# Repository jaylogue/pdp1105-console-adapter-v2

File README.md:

# PDP-11/05 Console Adapter

The *PDP-11/05 Console Adapter* is a hardware device which acts as a USB and RS-232 serial interface to the console of a [PDP-11/05](http://gunkies.org/wiki/PDP-11/05) minicomputer. The Console Adapter provides a number of useful features for working with the PDP-11/05:

- **Direct connection to the SCL connector on the back of the PDP-11/05**
- **USB-to-serial functionality, allowing access to the PDP-11 console from a modern terminal program**
- **Auxiliary RS-232 interface for connecting a real serial terminal**
- **External baud clock generator, allowing console data rates greater than 2400 bps**
- **Dynamically adjustable serial data rate and format (110 to 38400 bps, 8-N-2, 7-E-2, 7-O-2)**
- **Virtual paper tape reader compatible with the 11/05's READER RUN signal**
- **M9312/M9301 console loader that can directly load data into the PDP-11's memory using console commands**

This version of the PDP-11/05 Console Adapter project (version 2) is based on the ubiquitous [Raspberry Pi Pico](https://www.raspberrypi.com/products/raspberry-pi-pico/) microcontroller. An earlier version based on the Teensy 3.2 microcontroller can be found [here](https://github.com/jaylogue/pdp-1105-console-usb-adapter).

### Project Status (2025/07/29)

The first major release of the PDP-11/05 Console Adapter is ready. The schematic and PCB designs are finished and final hardware has been built. The firmware is feature complete and tested, and user documentation has been written. Two different 3D-printed enclosures have been designed and built, and the design files for these are available for download.

I am happy to make assembled hardware or kits available to those enthusiasts who own real PDP-11/05 or /10 systems. Please reach out to me at jay DOT logue AT gmail DOT com for details.

<hr>

**[How it Works](#how-it-works)**<br>
&nbsp;&nbsp;&nbsp;&nbsp;&nbsp;&nbsp;&nbsp;&nbsp;**[Console Interface](#console-interface)**<br>
&nbsp;&nbsp;&nbsp;&nbsp;&nbsp;&nbsp;&nbsp;&nbsp;**[Auxiliary Terminal Interface](#auxiliary-terminal-interface)**<br>
&nbsp;&nbsp;&nbsp;&nbsp;&nbsp;&nbsp;&nbsp;&nbsp;**[Baud Clock Generation](#baud-clock-generation)**<br>
&nbsp;&nbsp;&nbsp;&nbsp;&nbsp;&nbsp;&nbsp;&nbsp;**[Host Selectable Data Rate / Serial Format](#host-selectable-data-rate--serial-format)**<br>
&nbsp;&nbsp;&nbsp;&nbsp;&nbsp;&nbsp;&nbsp;&nbsp;**[Status LEDs](#status-leds)**<br>
&nbsp;&nbsp;&nbsp;&nbsp;&nbsp;&nbsp;&nbsp;&nbsp;**[Power Source](#power-source)**<br>
&nbsp;&nbsp;&nbsp;&nbsp;&nbsp;&nbsp;&nbsp;&nbsp;**[Virtual Paper Tape Reader](#virtual-paper-tape-reader)**<br>
&nbsp;&nbsp;&nbsp;&nbsp;&nbsp;&nbsp;&nbsp;&nbsp;**[M9312/M9301 Console Loader](#m9312m9301-console-loader)**<br>
&nbsp;&nbsp;&nbsp;&nbsp;&nbsp;&nbsp;&nbsp;&nbsp;**[On-device File Library](#on-device-file-library)**<br>
&nbsp;&nbsp;&nbsp;&nbsp;&nbsp;&nbsp;&nbsp;&nbsp;**[XMODEM File Upload](#xmodem-file-upload)**<br>
**[Schematic](#schematic)**<br>
**[PCB Design Files](#pcb-design-files)**<br>
**[3D Printable Cases](#3d-printable-cases)**<br>
**[User Documentation](#user-documentation)**<br>
**[License](#license)**<br>

## How it Works

### Console Interface

At the most basic level, the Console Adapter operates as a TTL-serial interface, connecting the PDP-11's console (also known as the Serial Communication Line or SCL port) to one of the Pico's internal UARTs. Level shifting circuitry in the adapter adjusts the PDP's 5V outputs to match the Pico's 3.3V inputs. Using USB software on the Pico, the adapter appears as a virtual COM port when connected to a host computer via USB, making it possible to use a standard terminal program (e.g. minicom, picocom or PuTTY) to interact with the PDP's console. In this way, the Console Adapter operates very similarly to an off-the-shelf USB-to-TTL serial device, with the exception that its behavior is fully customizable in software.

The Console Adapter supports standard serial data rates in the range accepted by the PDP-11 (110 to 38400 bps). Internally, the CPU in the PDP-11/05 is hard-wired to use the 8-N-2 serial format. However, with appropriate software support on the PDP side, 7-E-2 or 7-O-2 formats can also be used (other formats are not supported). Based on this, the Console Adapter limits the SCL format to one of these three combinations.

### Baud Clock Generation

The PDP-11/05 CPU includes a clock generator circuit which is used to generate the 16X clock signal needed to drive the internal console UART chip. Due to its simplicity, the internal generator limits the maximum usable data rate to 2400 bps. Conveniently, the PDP-11/05 provides a way to override the internal generator by providing an external clock signal on the SCL port. This allows the console to run at substantially higher data rates (theoretically up to 40000 bps).

To enable higher data rates, the Console Adapter employs a PWM peripheral on the Pico to generate the necessary clock signal to drive the PDP's UART. The frequency of this clock signal is automatically adjusted to match the data rate of the Pico's UART, ensuring that the two systems are always in sync.

### Auxiliary Terminal Interface

In addition to the host USB interface, the Console Adapter provides a second interface which can be used to connect a traditional serial terminal such as a VT-100. An RS-232 level shifter (MAX3232) is used to convert the signals to standard EIA levels, allowing most terminals of the era to be used. When connected, the terminal functions as an additional console for the PDP-11.

An auxiliary terminal can be used in parallel with a terminal program connected via USB. When operated this way, characters typed on either the host computer or the auxiliary terminal are forwarded to the PDP-11, while characters output by the PDP-11 appear simultaneously on both terminals. It is also possible to use the Console Adapter with just an auxiliary terminal connected (i.e. without a host USB connection).

The data rate and serial format for the auxiliary terminal can be set independently from that of the PDP-11's SCL port. (Although, since neither interface supports flow control, it is best to keep the data rates the same or similar between the two.)

### Host Selectable Data Rate / Serial Format

The Console Adapter appears to the host computer as a standard USB COM device. As such, it is able to receive and process standard USB requests to change the serial configuration (also known as CDC Line Coding requests). This makes it possible to adjust the adapter's serial data rate and format directly from within terminal software running on the host.

When the Console Adapter receives a Line Coding request it adjusts the configuration of the console UART and baud clock generator to match the requested data rate and serial format. Serial configuration changes happen on the fly and can be made at any time. If desired, the auxiliary terminal interface can also be set to automatically adjust to the new configuration.

The PDP-11/05's SCL port is hard-wired to use 2 stop bits. This format is somewhat unusual in modern systems, and most terminal programs default to a format using 1 stop bit (usually 8-N-1). As a convenience to the user, the Console Adapter accepts USB Line Coding requests for 1 stop bit formats and internally translates them into the equivalent 2 stop bit format when configuring the SCL port.

The choice to dynamically adjust the serial configuration based on a request from the host can be enabled or disabled independently for both the SCL and auxiliary terminal ports. When this feature is disabled, the serial configuration is controlled by a setting in the Console Adapter's settings menu. These settings are persisted in flash and survive adapter reboots.

### Status LEDs

The PDP-11/05 Console Adapter has three status LEDs:

- **Power/Activity LED**: Lit while the system is powered. Flashes briefly whenever there is activity in the Console Adapter.
- **TX and RX LEDs**: Normally off. Flash on whenever characters are transmitted/received by the PDP-11.

Additionally, the Pico's onboard LED mimics the behavior of the Power/Activity LED.

### Power Source

The Console Adapter operates on +5 volts, which it can receive either from the PDP-11/05 itself or via the USB port. Because the Console Adapter can get its power directly from the PDP, it is possible to use the Console Adapter with only an auxiliary terminal connected.

Both power sources can be active at the same time, and the USB port can be connected or disconnected on the fly. (However, **_do not_** hot plug/unplug the Console Adapter to the 11/05's SCL port, as it is not designed to support this.)

### Virtual Paper Tape Reader

The PDP-11/05 SCL port includes a signal called "READER RUN" which is designed to drive a low-speed paper tape reader attached to the console device (the quintessential example being the [ASR-33 teletype](https://en.wikipedia.org/wiki/Teletype_Model_33)). Whenever the PDP asserts the "READER RUN" signal, the reader is expected to read one character from a mounted paper tape and send it to the computer. In the Console Adapter, the READER RUN signal drives a transistor whose output is fed to a GPIO pin on the Pico. Software on the Pico detects READER RUN transitions and uses this to emulate the behavior of a legacy tape reader.

Users can mount paper tape images on the virtual paper tape reader using the Console Adapter's menu system (accessed by typing a special _menu_ key on the console). While the tape reader is active, a visual progress bar is displayed showing how much of the tape image has been read. Virtual tapes are unmounted automatically when the end of the tape is reached, or can be unmounted manually via the UI.

### M9312/M9301 Console Loader

On systems equipped with an M9312 or M9301 Bootstrap Terminator module, the PDP-11/05 Console Adapter can be used to load data files directly into the PDP's memory using the UI provided by the module's console ROM. Data is loaded by issuing a series of Load Address (L) and Deposit (D) commands and monitoring the responses received from the console. The loader automatically detects data files in Absolute Loader (LDA) format and arranges to load their contents at the correct memory offsets.

The loader includes special support for loading the PDP-11 Bootstrap Loader (the code for which is built into the Console Adapter firmware). When requested to load the Bootstrap Loader, the Console Adapter will prompt the user for the memory size of the machine and adjust the software's load address and instruction contents automatically, following the rules described in the associated DEC documentation.

A similar feature is available for loading the Absolute Loader, which allows for bypassing the Bootstrap Loader step completely.

### On-device File Library

The Console Adapter supports the ability to load frequently used paper tape images and other types of data files into the Pico's flash memory such that they are readily available for use when working with the PDP-11. A Python-based command line tool is provided that gathers a set of data files into a .uf2 file which can then be written to flash using one of the standard Pico firmware update processes (e.g. by dragging it onto the Pico's virtual disk). Once programmed in flash, files in the library are available for mounting on the virtual paper tape reader, or loading directly into memory using the M9312/M9301 console loader feature.

1MiB of flash memory is available for file storage. Up to 36 files may be stored in this memory, with each file limited to a maximum of 128KiB.

### XMODEM File Upload

In addition to files stored in flash, data files can be uploaded to the Console Adapter using the XMODEM file transfer protocol. Files can be uploaded either via the USB interface or the auxiliary terminal interface using appropriate XMODEM software on the sending side. Once uploaded, a file can be used repeatedly for mounting on the virtual paper tape reader or loading via the console loader.

Uploaded files are stored in RAM on the Console Adapter and are limited to 64KiB in size.

## Schematic

The following diagram shows the schematic for the PDP-11/05 Console Adapter:

A PDF version of the schematic is available [here](docs/pdp1105-console-adapter-schematic.pdf).

Note that the Console Adapter schematic uses modern pin numbering for the console IDC connector (J1), rather than the archaic DEC letter-based scheme. For a table showing the relationship between the two numbering schemes, see the following PDF: [pdp1105-scl-connector.pdf](docs/pdp1105-scl-connector.pdf).

## PCB Design Files

A KiCad project containing the schematic and a layout file for a two-layer PCB is available in the [pcb](pcb) folder.

## 3D Printable Cases

The [case](case) folder contains model and design files for a set of 3D-printable cases for the Console Adapter. Two case styles are provided: a **standalone case** and a **direct attach case**. Each style consists of a bottom 'base' piece and a top 'cover' piece. The lettering visible on the case is embossed into the top piece. A separate design file is included which allows this lettering to be filled with a different color on printers that support swapping filaments.

The standalone case allows the Console Adapter to be connected to the PDP-11/05 using a ribbon cable. A hole on the side of the case accommodates a right-angle 40-pin male IDC connector, which is mounted on the top of the PCB. The two halves of the standalone case snap together, holding the PCB in place.

The direct attach case has a hole on the bottom of the case through which a female 40-pin connector protrudes. The connector is soldered to the bottom of the PCB, and extends from the back of the case far enough to allow the adapter to plug directly into the PDP's SCL port. A flange with a screw hole allows the case to be anchored to the back of the system using an existing case screw.

The direct attach case is held together with two small screws which pass through the PCB.

## User Documentation

A User Manual for the PDP-11/05 Console Adapter is available [here](docs/pdp1105-console-adapter-user-manual.md).

## License

The PDP-11/05 Console Adapter source code is licensed under the [Apache version 2.0 license](https://www.apache.org/licenses/LICENSE-2.0).

Other content, including all documentation, images, schematics, PCB and case designs, and this README file, is licensed under a [Creative Commons Attribution 4.0 International License](https://creativecommons.org/licenses/by/4.0/).

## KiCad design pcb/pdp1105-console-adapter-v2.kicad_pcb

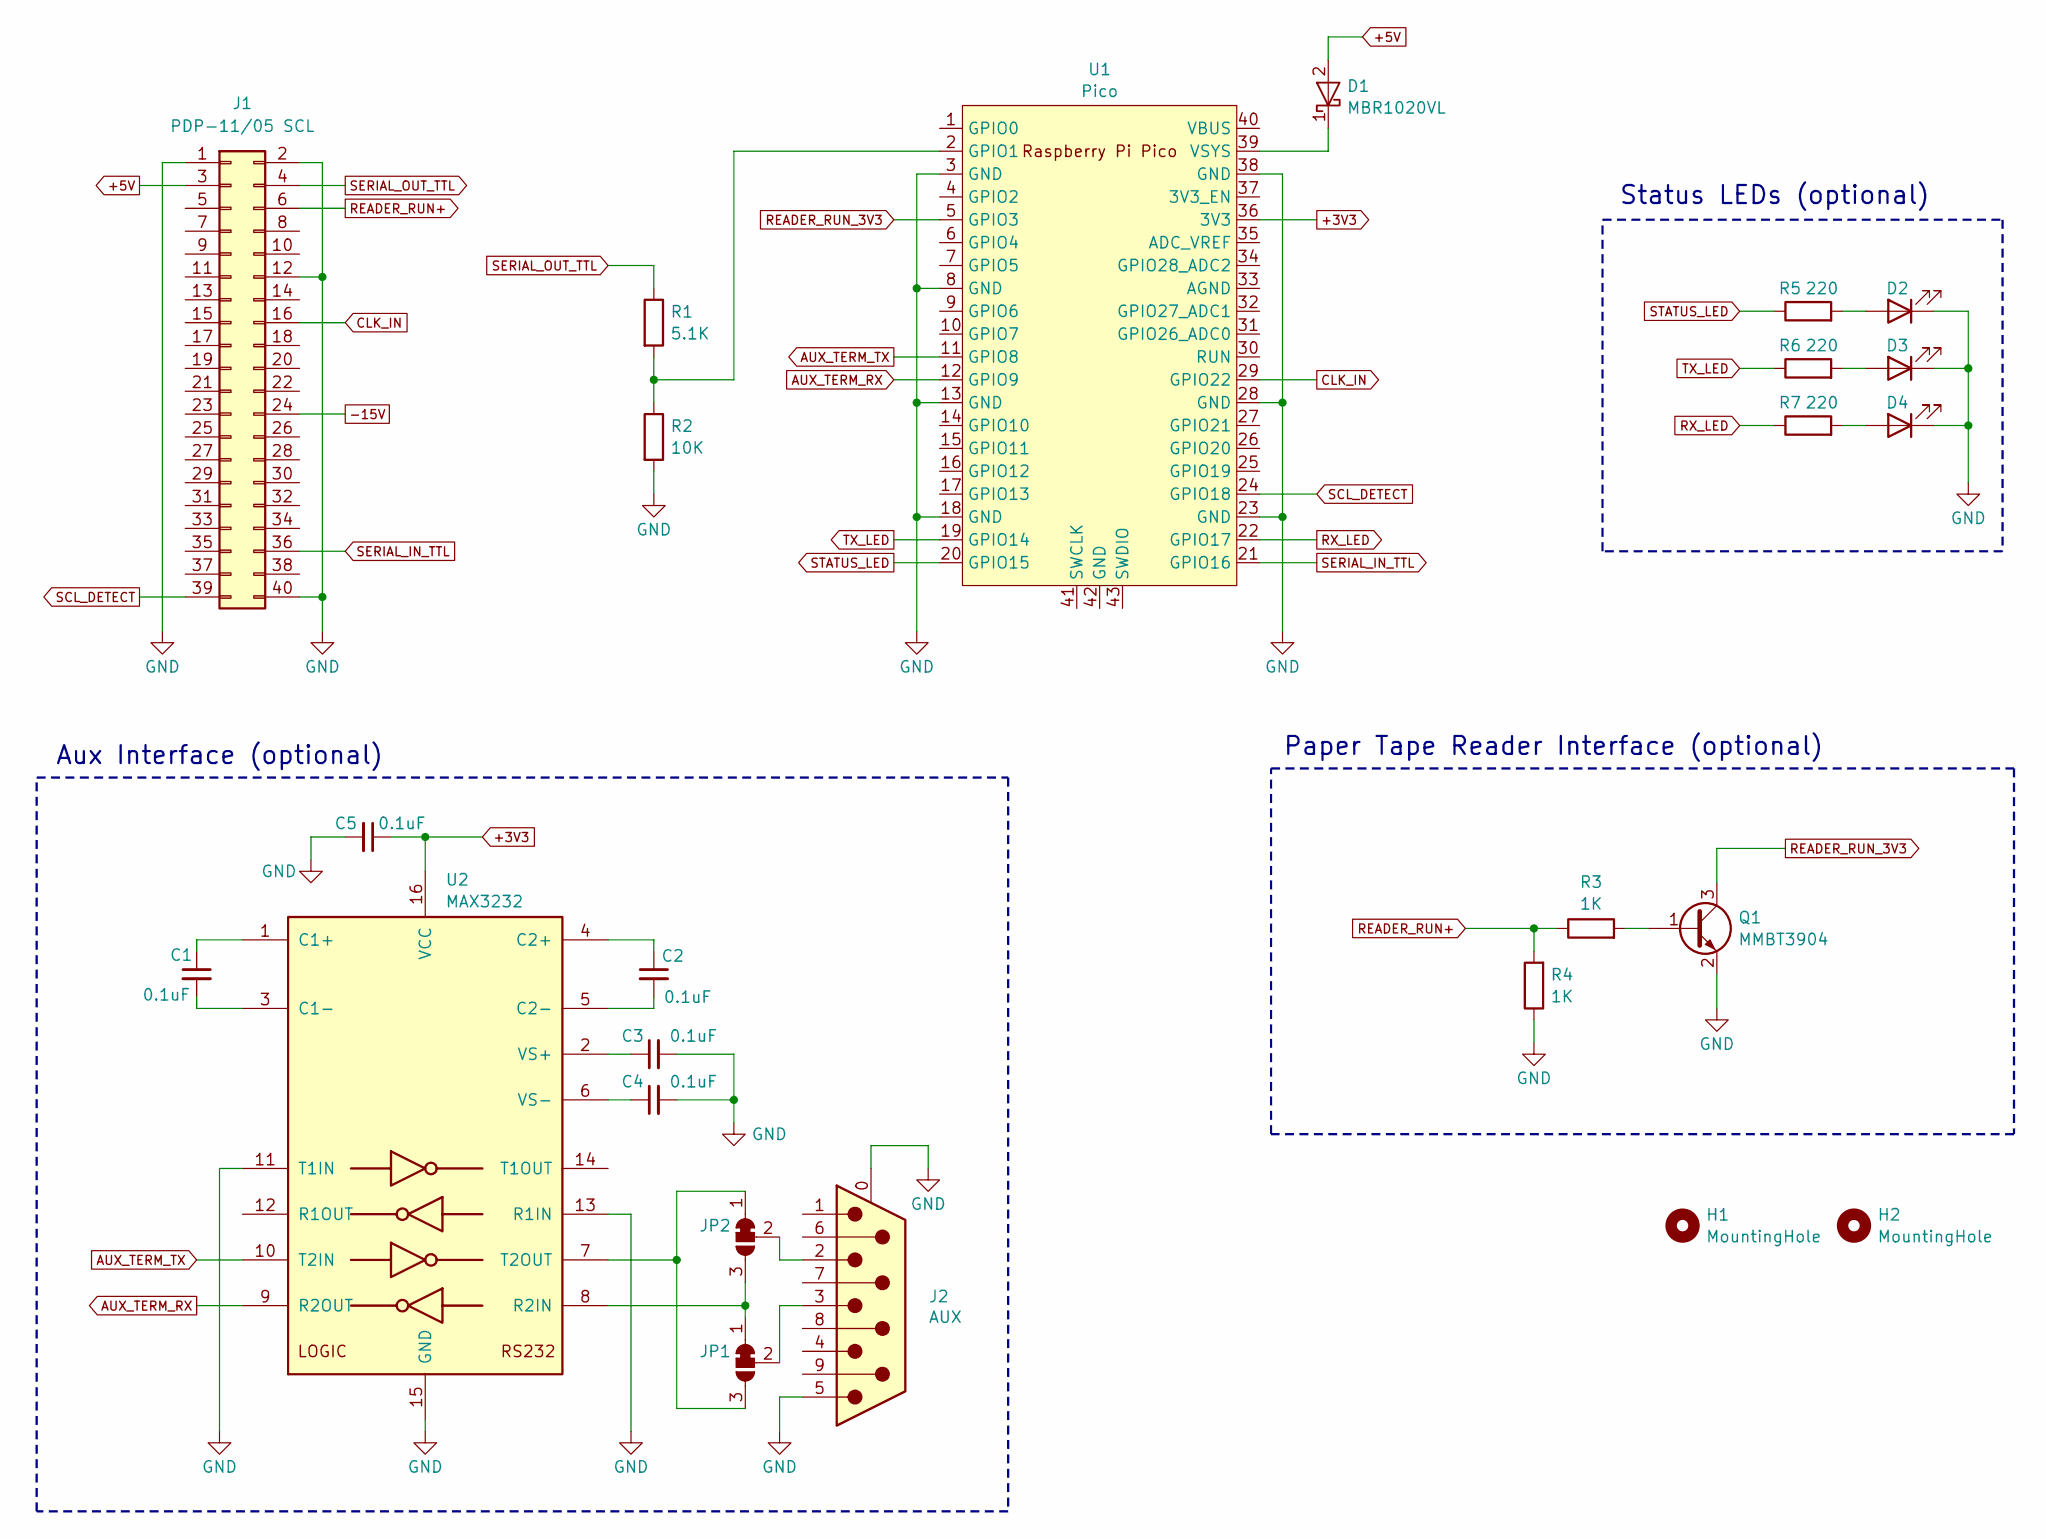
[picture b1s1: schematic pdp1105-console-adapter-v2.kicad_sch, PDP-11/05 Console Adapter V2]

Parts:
C1, C2, C3, C4, C5: 0.1uF; C_0805_2012Metric_Pad1.18x1.45mm_HandSolder; LCSC C28233
D1: MBR1020VL; D_SOD-123F; LCSC C391533
D2, D3, D4: LED; LED_D5.0mm
H1, H2: MountingHole; MountingHole_2.7mm_M2.5
J1: PDP-11/05 SCL; PinSocket_2x20_P2.54mm_Vertical
J2: AUX; DSUB-9_Female_Horizontal_P2.77x2.84mm_EdgePinOffset7.70mm_H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
JP1, JP2: SolderJumper_3_Bridged12; SolderJumper-3_P1.3mm_Bridged12_Pad1.0x1.5mm
Q1: MMBT3904; SOT-23; LCSC C20526
R1: 5.1K; R_0805_2012Metric_Pad1.20x1.40mm_HandSolder; LCSC C27834
R2: 10K; R_0805_2012Metric_Pad1.20x1.40mm_HandSolder; LCSC C17414
R3, R4: 1K; R_0805_2012Metric_Pad1.20x1.40mm_HandSolder; LCSC C17513
R5, R6, R7: 220; R_0805_2012Metric_Pad1.20x1.40mm_HandSolder; LCSC C17414
U1: Pico; RaspberryPi_Pico_Common_THT
U2: MAX3232; SOIC-16_3.9x9.9mm_P1.27mm; LCSC C9378

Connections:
+3V3: C5.1, U1.36 (3V3), U2.16 (VCC)
+5V: D1.2 (A), J1.3 (+5V)
-15V: J1.24 (-15V)
AUX_TERM_RX: U1.12 (GPIO9), U2.9 (R2OUT)
AUX_TERM_TX: U1.11 (GPIO8), U2.10 (T2IN)
CLK_IN: J1.16 (CLK_IN), U1.29 (GPIO22)
GND: C3.2, C4.2, C5.2, D2.1 (K), D3.1 (K), D4.1 (K), J1.1 (GND), J1.2 (GND), J1.12 (CLK_DISAB), J1.40 (GND), J2.0 (PAD), J2.5, Q1.2 (E), R2.2, R4.1, U1.3 (GND), U1.8 (GND), U1.13 (GND), U1.18 (GND), U1.23 (GND), U1.28 (GND), U1.38 (GND), U2.11 (T1IN), U2.13 (R1IN), U2.15 (GND)
unnamed: D1.1 (K), U1.39 (VSYS)
unnamed: D2.2 (A), R5.2
unnamed: D3.2 (A), R6.2
unnamed: D4.2 (A), R7.2
unnamed: JP1.1 (A), JP2.3 (B), U2.8 (R2IN)
unnamed: JP1.3 (B), JP2.1 (A), U2.7 (T2OUT)
unnamed: J2.3, JP1.2 (C)
unnamed: J2.2, JP2.2 (C)
unnamed: Q1.1 (B), R3.2
unnamed: R1.2, R2.1, U1.2 (GPIO1)
unnamed: C1.1, U2.1 (C1+)
unnamed: C1.2, U2.3 (C1-)
unnamed: C2.1, U2.4 (C2+)
unnamed: C2.2, U2.5 (C2-)
unnamed: C3.1, U2.2 (VS+)
unnamed: C4.1, U2.6 (VS-)
READER_RUN+: J1.6 (+READER_RUN_20MA), R3.1, R4.2
READER_RUN_3V3: Q1.3 (C), U1.5 (GPIO3)
RX_LED: R7.1, U1.22 (GPIO17)
SCL_DETECT: J1.39 (GND), U1.24 (GPIO18)
SERIAL_IN_TTL: J1.36 (SERIAL_IN_TTL), U1.21 (GPIO16)
SERIAL_OUT_TTL: J1.4 (SERIAL_OUT_TTL), R1.1
STATUS_LED: R5.1, U1.20 (GPIO15)
TX_LED: R6.1, U1.19 (GPIO14)

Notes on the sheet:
Aux Interface (optional)
Status LEDs (optional)
Paper Tape Reader Interface (optional)

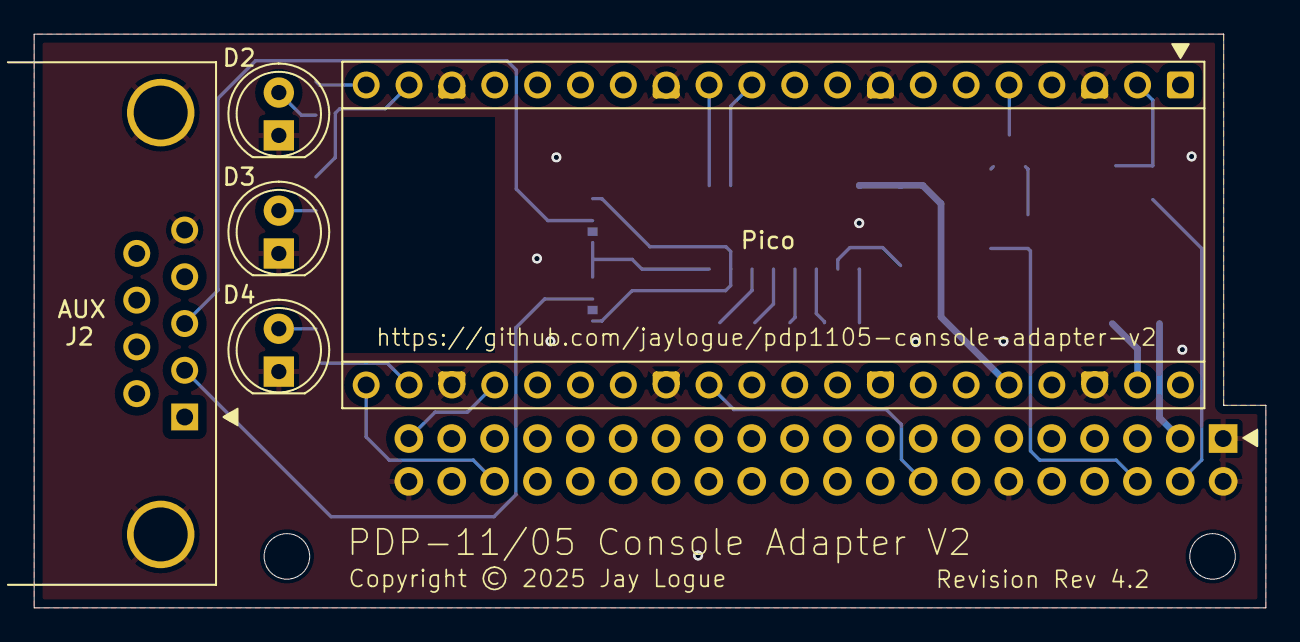
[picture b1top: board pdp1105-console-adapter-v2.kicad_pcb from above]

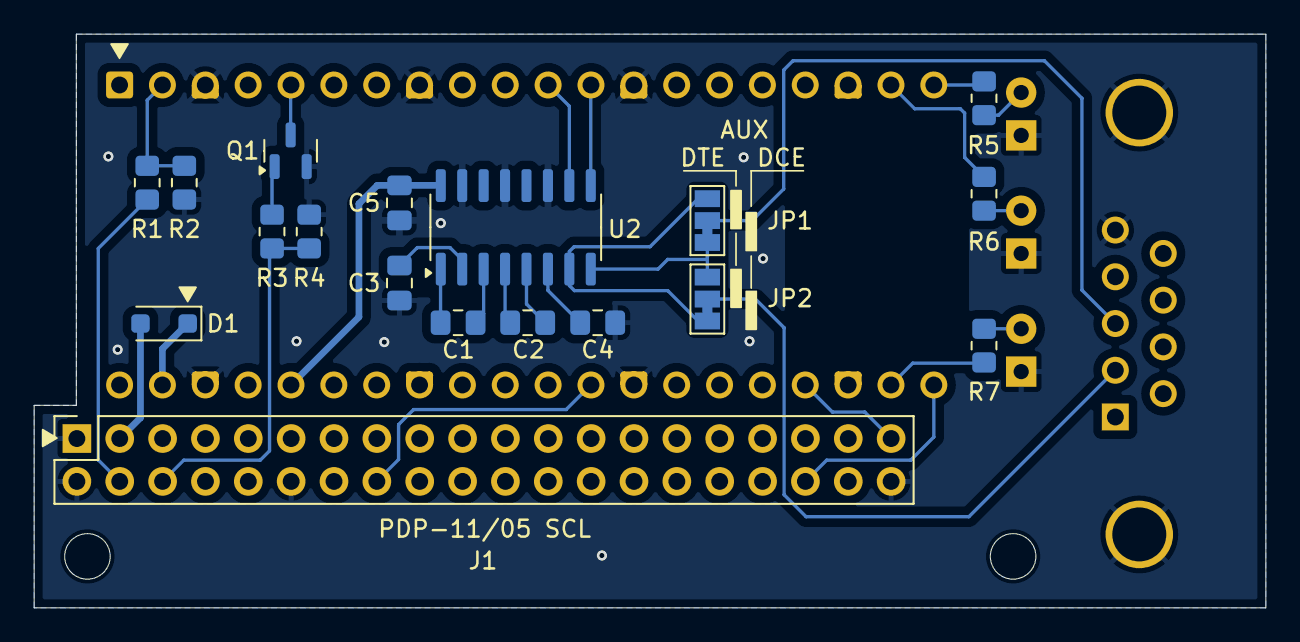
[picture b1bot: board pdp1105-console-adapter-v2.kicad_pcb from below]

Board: 2 copper layers, 73.0 x 34.0 mm, 25 parts (18 on the bottom side), 30 nets.

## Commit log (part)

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2024-09-07 Initial version
    -- Initial working version of PDP-11/05 Console USB Adapter for the Raspberry
    Pi Pico. All major features have been implemented and tested on prototype
    hardware with the exception of the READER RUN interface.
2024-09-14 Preliminary READER RUN support
2024-09-29 Final pin configuration for rev 3 schematic
2025-01-16 Schematic and PCB design files
2025-01-16 Placeholder images
2025-03-16 Reorganize PCB design files
2025-03-16 ﻿Initial version of Rev 4 schematic
    -- Added status LEDs
    -- Changed Aux port connector to board-mounted DE9
    -- Added mounting hole components
2025-03-16 ﻿Initial version of Rev 4 PCB
    -- New PCB board outline
    -- Basic placement of major components: Pico, SCL connector, DE9, LEDs and
    mounting holes.
    -- No other components placed. No traces routed.
2025-03-16 ﻿Absolute Loader support
    -- Support for mounting a built-in paper tape image of the Absolute Loader
    -- Support for loading the Absolute Loader into memory using the M9301/M9312
    console.
    -- Minor clean-ups to Bootstrap Loader code.
2025-03-16 ﻿More major changes
    -- Introduced Port base class and made port objects virtual. Create global
    objects for the three ports: Host USB, Aux terminal and SCL. Revised all
    other code to use these objects.
    -- Revised Menu Mode code to present UI on the port that the menu character
    was received on (Host USB or Aux terminal). This choice then follows through
    to all other modes that have UI (e.g. Load Data Mode).
2025-03-16 Python script to emulate M9312 console. Useful for testing Load Data Mode.
2025-03-16 ﻿Paper tape file set builder tool
    -- Command line tool to build a paper tape file set that can be directly flashed
    onto the Console Adapter. The tool takes a list of paper tape files and encodes
    them into a UF2 file that can be dragged to the Pico’s USB filesystem or flashed
    with the picotool.
2025-03-16 Restructured some constants.
2025-03-16 WIP Menu Mode (incomplete/un-tested)
2025-03-16 ﻿Load Data Mode changes
    -- Support loading the bootstrap loader at different memory locations
    -- Minor UI changes
2025-03-16 Add KeySeqMatcher class with unit tests
    -- The KeySeqMatcher class matches a stream of input characters against a set of
    predefined key sequences. The class supports detecting complete key sequences,
    tracking partial matches, timing out partial matches, and returning unprocessed
    characters when matches fail.
    -- Implemented unit tests for the KeySeqMatcher class. The unit tests can be
    compiled as a standalone executable with the -DUNIT_TEST flag.
2025-03-16 ﻿Work on M9301/M9312 controller
    -- Implemented new mechanism for prompt synchronization based on using a
    sync character.
    -- Added validation of characters received from the M9301/M9312 console
    and error handling for unexpected characters.
    -- Minor changes to timer handling.
2025-03-16 Source tree reorganization
2025-03-16 ﻿M9301/M9312 Console Controller
    -- Implemented the M93xxController class, which provides an API for driving
    an M9301/M9312 console via the serial interface.
    -- Implemented unit test code for the M93xxController which can be compiled
    as a stand-alone executable using the -DUNIT_TEST flag.
    -- Implemented dummy version of LoadFileMode to test the M93xxController
    class running on the console adapter hardware. The code was tested against
2025-03-16 ﻿Modified the M9312 simulator to more properly emulate the end-of-line behavior of the original
2025-03-16 Additional work on menu mode
    -- Added code to listen for multi-character menu key sequences and enter menu mode
    when detected. Currently the code has sequences for TVI-912, TVI-920, VT100 and
    ANSI/VT220+ terminals.
    -- Added skeletal file load and upload modes.
    -- Discarded old MenuKeyMonitor class.
2025-03-16 Support for loading PDP-11 bootstrap loader via M9301/M9312 console
2025-03-16 ﻿Work on M9301/M9312 load data mode
    -- Implemented LDADataSource class which parses Absolute Loader files and delivers
    addresses and data values for direct transfer to memory via the M9301/M9312
    console interface
    -- Renamed data source for loading the PDP-11 bootstrap loader
    -- Added Name interface to data source base class and subclassses
    -- Added ability to select a source file for load data mode
2025-03-16 Eliminate MemFile class
2025-03-16 ﻿Support for loading simple data files (files that aren’t Absolute Loader files or otherwise special).
2025-03-16 ﻿Enhancements to M93xxController and Load Data Mode
    -- Automatically abort Load Data Mode if the system is unable to get a prompt
    from the M9301/M9312 console emulator within a reasonable amount of time.
    -- Establish synchronization with the M9301/M9312 console upon start of Load
    Data Mode. This ensures the console is in the right state to accept commands.
2025-03-16 ﻿Move file name out of LoadDataSource and pass as argument to LoadDataMode()
2025-03-16 More work on menu mode
    -- Backtracked on use of multi-character key sequence for menu mode. Menu mode
    now entered using Ctrl+^.
    -- Introduced I/O helper functions to make interactions with host terminal and
    UARTs more readable.
2025-03-18 ﻿Restructured Menu Mode code
    -- Created general mechanism for rendering menus and prompting for a
    selection.
    -- Created general mechanism for selecting files
    -- Rearranged file menu presentation and added support for case where
    no user-installed files are present
2025-03-20 ﻿Use interrupts instead of polling to detect a change in the READER RUN signal.
2025-03-20 ﻿Diagnostic Mode
    -- Added hidden menu with diagnostic tests
    -- Implemented test to validate basic input/output via the SCL port.
    -- Implemented test to validate correct operation of the paper tape
    READER RUN interface.
2025-03-20 Implemented a visual progress bar for the paper tape reader
2025-03-20 ﻿Added support for external activity LEDs
    -- Implemented support for external Tx and Rx activity LEDs. These signal when
    the SCL port is transmitting or receiving characters.
    -- Implemented support for an extern system activity LED. This serves as both
    a power indicator and a signal of activity on the USB host or Aux ports. The
    Pico onboard LED mirrors the state of this LED.
    The GPIO numbers assigned to the new external LEDs are provisional until the new
2025-03-23 ﻿Refactored menu code
2025-03-23 ﻿Various changes
    -- More menu code refactoring
    -- Changed text of Settings menu for clarity
    -- Separated default serial configs for SLC vs Aux ports
    -- Created PTRProgressBar class to encapsulate progress bar display logic
    -- Print name of paper tape file when mounted
    -- Other minor editorial changes
2025-03-24 ﻿Adapter status
    -- Added a general Adapter status option to main menu that shows the status of
    the SCL and Aux ports and the virtual paper tape reader.
    -- Removed the Paper tape status option.
2025-03-27 ﻿Support for persistent storage of console adapter settings
    -- Implemented application-specific linker script. Added reserved sections
    in flash for adapter settings (8KB) and file set storage (1MB).
    -- Enhanced Settings class to support storing adapter settings in flash.
    Features include wear-leveling of flash sectors and a simple schema
    versioning mechanism.
    -- Modified FileSet class to use linker-defined file set storage area.
2025-03-27 ﻿Minor changes to mktapefileset.py
    -- Enforce maximum size of file set image in flash
    -- Compute default base address for file set image in flash based on
    overall flash memory size.
    -- Change references to "flash page" to refer to "flash sector"
    instead.
2025-03-27 Created project .gitignore
2025-03-27 Default paper tape file set image
2025-03-27 Tool to dump contents of PDP-11 Absolute Loader (LDA) files
2025-03-27 ﻿Removed extraneous compiler directives used for debugging
2025-03-31 ﻿General clean up
    -- Enabled and fixed-up various compiler warnings.
    -- Disabled potentially troublesome compiler optimization.
2025-04-02 ﻿Completed layout and routing for revision 4 PCB
    -- NOTE: Pico pin assignments were altered from revision 3 board to simplify routing
2025-04-03 ﻿Display whether the SCL port is connected in the Adapter Status output
2025-04-04 ﻿Updates to rev 4 PCB layout
    -- Moved SMT components to back side of PCB to facilitate rework when Pico
    is soldered in place.
2025-04-05 ﻿Firmware support for rev 4 PCB
    -- Added ability to build firmware for specific hardware revisions.
    -- Modified default GPIO assignments to match rev 4 schematic.
    -- Added support for building rev 3 compatible firmware.
    -- Added target hardware revision to Adapter Version output.
2025-04-05 Update schematic PDF to rev 4
2025-04-12 Revision 4.1 Schematic and PCB Design
    -- Switch to female DE9 connector for Aux port.
    -- Added solder jumpers to select between DTE and DCE configuration for Aux
    port. Default is set to DCE.
    -- Revised LED component layout to allow for copper keep-out area under
    Pico W antenna.
    -- Added copper ground fill on PCB backside.
2025-04-12 ﻿Firmware support for rev 4.1 PCB
    -- Swap GPIOs for System Status and Tx LEDs
    -- Generalized HW_REV #define to support minor revisions
2025-04-25 ﻿Minor UI changes
    -- Generalized the menu prefix string to be a “title” prefix that is
    used to identify notable UI output. Use this consistently across the
    UI code.
    -- Made INPUT_PROMPT and TITLE_PREFIX compile-time configuration items.
2025-04-25 ﻿Revision 4.2 Schematic and PCB Design
    -- Fixed bug in schematic that resulted in the AUX port defaulting to DTE
    configuration instead of DCE.
    -- Fixed bug in PCB silkscreen that mislabeled the jumper configuration for
    choosing AUX port DTE vs. DCE configuration.
    Note that revision 4.2 is firmware compatible with revision 4.1.
2025-04-25 ﻿Added list of compatible hardware revisions to the console adapter version display.
2025-04-28 Initial README
2025-04-28 Edits to README file
2025-04-28 More edits to README file
2025-06-11 ﻿Various changes
    -- Renamed files and updated code and documentation to consistently use the
    term "file library" to refer to files stored in flash.
    -- Fixed bug in menu mode that displayed incorrect selector character when
    file library contained more than 10 files.
    -- Update default file library image to include PAL-11 and associated paper
    tape images.
2025-06-13 ﻿Changes to UI to align with documentation
    -- Use context-specific menu names when selecting files to load or mount
    as paper tapes.
    -- Use "AUX" to refer to auxiliary serial port.
    -- When inputting integers, display the default value in the input field
    until the first character is typed.
    -- Don't use "interface" in progress bar setting menu.
2025-06-14 ﻿Initial version of user manual
    -- Created initial version of user manual markdown file and associated
    images
    -- Consolidated documentation images into docs/media
    -- Removed some unused images
    -- Updated README
2025-06-14 ﻿More work on documentation
    -- Switch to inline code formatting for key sequences
    -- Added caution about grounding
    -- Other minor formatting and editorial changes
2025-06-15 Uppercase Mode
    -- Added mode in which all characters sent to the SCL port are converted to
    uppercase.
    -- Added Uppercase Mode setting.
    -- Modified the settings code to use the term "active" when referring to the
    record in flash that contains the most current settings, and "latest" when
    referring to the SettingsRecord subclass with the highest version
2025-06-15 Added documentation for uppercase mode to user manual
2025-06-15 Updated user manual with picture showing correct orientation of SCL cable
2025-06-15 Move schematic PDF to docs directory
2025-06-15 Updated project status
2025-06-15 Added copyright to user manual
2025-07-13 Reorg case design files
2025-07-13 ﻿Small change to the default file library
    -- Updated the example BASIC program included in the default file library
    (CALCULATE PI) to so that it matches what would be output by the BASIC SAVE
    command. In particular, the file now uses CR/LF line endings and has a
    trailer of nul bytes.
2025-07-13 ﻿Virtual paper tape reader unmount change
    -- Modified the automatic unmount behavior of the virtual paper taper
    reader such that the paper tape is unmounted at the moment the PDP-11
    outputs the first character after the tape has been fully read. This
    gives the user a chance to see the reader progress bar advance to 100%
    before being cleared from the screen.
    On effect of this is that, when reading a BASIC program using the OLD

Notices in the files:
pcb/pdp1105-console-adapter-v2.kicad_pcb:
Copyright © 2025 Jay Logue
